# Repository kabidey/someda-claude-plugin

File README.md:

# someda for Claude Code

**Describe a circuit; get a fab-ready KiCad project with every claim checked.**

This plugin puts the [someda](https://github.com/kabidey/someda) engine behind three slash
commands. In a conversation, Claude writes the circuit as a small JSON plan: real parts with
datasheet pinouts, nets, and intent such as "USB-C on the top edge". Never a coordinate. The
compiled engine does the rest: schematic, footprints, placement, routing (differential pairs,
enforced crosstalk spacing), signal-integrity / stability / thermal audits, KiCad's own ERC and
DRC, Gerbers, drill, BOM, a JLCPCB order package and 3D renders. The build ends with six gates;
all six pass or the answer is **NOT DONE** with the failing gate named.

The engine repairs what a plan edit can fix (a misspelled footprint, a missing decoupling
capacitor, a regulator short of output capacitance, a connector with no room on its edge) and
builds again, so the plan can come from a small model, a large one, or a person.

## Install

```bash
claude plugin marketplace add kabidey/someda-claude-plugin
claude plugin install someda@someda
```

On first use the plugin resolves the engine: `someda` on your PATH, a `SOMEDA_BIN` override, or
the release binary for your platform (Linux x86_64, macOS Apple silicon and Intel, Windows
x86_64; other platforms are built from source with `cargo`). It also installs what a build
needs beyond the binary: KiCad's footprint and 3D model libraries (`apt` on Debian/Ubuntu) and
the LCSC/EasyEDA converter in a private virtualenv.

You need [KiCad](https://www.kicad.org/) with `kicad-cli` on your PATH (developed and verified
against KiCad 10.0.6). No API key is required: Claude is the planner.

Not using Claude Code? The same release archive the plugin downloads also holds `someda-app`,
a desktop window that does the whole flow with any language model provider (see the
[engine README](https://github.com/kabidey/someda#the-desktop-app)).

## What a session looks like

```
you:     /pcb-plan a 555 timer blinking an LED at about 1 Hz, 5 V in on a header
claude:  writes plan.json (NE555, timing RC, LED and resistor, 100 nF next to the 555,
         a 2-pin header on the left edge) and shows it for review

you:     /pcb-build 555 LED blinker
claude:  1. schematic written and exported to PDF for your approval
         2. fetch-libs: every footprint and 3D model FOUND or FETCHED (none MISSING)
         3. the engine builds: placement ✓  routed 15 of 15 ✓  audits ✓
            kicad-cli ERC ✓ DRC 0 errors ✓  Gerbers / drill / BOM / JLCPCB package / renders ✓
            export preflight: drc shorts unrouted pours gerbers drill = 6 / 6
         → someda-build/circuit.kicad_pcb, fab/, fab/jlcpcb/, render/, plan.built.json
```

Those numbers are the engine's quick-start plan
([examples/plan_555.json](https://github.com/kabidey/someda/blob/master/examples/plan_555.json))
built with someda 0.7.0 and kicad-cli 10.0.6.

## Commands

| Command | What it does |
|---|---|
| `/pcb-plan <description>` | Write `plan.json` following the [contract](skills/someda/references/CONTRACT.md) and show it. No build. |
| `/pcb-build <description>` | Schematic for approval → libraries fetched → build with the engine's repair rounds → honest report of every stage and gate. |
| `/pcb-check <file>` | The engine's DRC/ERC on an existing `.kicad_pcb` or `.kicad_sch`. |

The build step in detail:

1. **Schematic first.** The engine writes a readable schematic (library symbols, labelled pins) and stops; Claude exports it to PDF and asks you to approve or change the plan.
2. **Libraries.** `scripts/fetch-libs.py` pulls every footprint and 3D model the plan needs that your KiCad libraries lack: KiCad's GitLab repositories, LCSC/EasyEDA by `lcsc` part number (or `mpn`, resolved through JLCPCB's parts search), and KiCad zips you downloaded from UltraLibrarian, SnapEDA, Mouser or Digi-Key (`--import`). Every part ends **FOUND**, **FETCHED** (with its source) or **MISSING** with the plan edit to make. A MISSING name that is only a misspelling is corrected by the engine's first repair round; a part the libraries really lack is never guessed.
3. **Build.** `someda ai build` runs up to `SOMEDA_REPAIR_ROUNDS` (default 3) repair rounds by itself, printing `repair:` for what it changed and `suggest:` with the exact plan edit for what it could not; the plan as built is `someda-build/plan.built.json`.
4. **Report.** Claude reads the stage table and the audits and tells you what passed, what the warnings mean physically, and where the files are. It never claims done when a gate failed.

## What the engine does

Placement from real courtyards (mounting holes at their corners, edge connectors rotated so
their opening faces the edge and placed on it, parts next to the pins they share, keep-out
rings for fine-pitch escapes); routing on JLCPCB rules for 2, 4 or 6 layers with inner planes
and per-pad fanouts, escape vias for fine-pitch pins, differential pairs as coupled corridors
with matched lengths, 3W/5W crosstalk spacing enforced for every fast net; audits on the routed
copper (stray L/C, SWR, unterminated lines, crosstalk re-measured, decoupling loop inductance,
regulator and crystal checks, PDN |Z(f)|, junction temperatures, JLCPCB scope); kicad-cli ERC and
DRC judged from the report file; Gerbers, drill, position, detailed BOM, JLCPCB order package
(Protel-named zip, assembly BOM, CPL with rotation corrections), 3D renders with component
bodies. The [engine README](https://github.com/kabidey/someda#readme) has the full list and the
plan fields.

## A real board

[examples/sompi-v3s](examples/sompi-v3s) is an Allwinner V3s single-board computer planned this
way: 132 parts on 90 × 60 mm, six layers, USB-C, 10/100 Ethernet, microSD, SPI NOR, 40-pin LCD
and 24-pin MIPI camera FPCs, audio jack, GPIO header, two bucks and two LDOs. With someda 0.7.0
it routes 187 of 187 connections, couples all seven USB / Ethernet / MIPI pairs within their skew
budgets, has 0 crosstalk violations and kicad-cli DRC 0 errors, and passes the six gates. The
engine rotated every edge connector from its footprint, moved the audio jack to the bottom edge
when the top edge had no slot deep enough, and grew the 1.8 V plane island to reach its
capacitors. Its remaining warnings are real and listed (crystal traces of 11–17 mm, one far
capacitor, three capacitors beyond the island, board density 147 %).

The unedited outputs of that build (Gerbers, KiCad project, DRC and ERC reports, schematic PDF,
renders, BOM, JLCPCB package, checksums) are in
[examples/sompi-v3s/evidence](examples/sompi-v3s/evidence).

## What "six gates" does not mean

The boards are not simulated and have not been built. Connector pinouts follow conventions that
must be checked against the parts you buy; 3D bodies fetched from LCSC are not verified against
physical parts; clock-to-data skew across pairs is not enforced; everything is placed on the
top side. Read the warnings; they are the engine telling you what it could not make good.

## Repository

```
commands/            pcb-plan, pcb-build, pcb-check
skills/someda/       SKILL.md: how Claude plans and runs a build; references/CONTRACT.md: the plan
scripts/             setup-someda.sh (engine + libraries), fetch-libs.py (footprints and 3D models)
examples/sompi-v3s/  the SBC plan, its generator, design notes and build evidence
```

MIT license · [SomTronics](https://somtronics.org)

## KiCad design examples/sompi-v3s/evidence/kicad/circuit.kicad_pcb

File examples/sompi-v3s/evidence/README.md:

# Build evidence — SomPi-V3s

Unedited outputs of one `someda ai build` run of `../plan.json`, kept here so the result in the
README can be checked rather than believed. Nothing in this directory was hand-edited after the
build. This is the 0.7.0 build: every differential pair routed as a coupled pair with its
measured intra-pair skew, 3W/5W crosstalk spacing enforced by the router and re-measured by the
audit, and the oscillation checks (termination, decoupling loops, regulators, crystals, PDN)
in the stage table.

## Provenance

| What | Value |
|---|---|
| Date | 2026-10-19 |
| Engine | kabidey/someda commit `1d11b951fee7` (Cargo version 0.7.0), `cargo build --release` |
| Plan | `examples/sompi-v3s/plan.json` from `gen_sompi.py` |
| Verifier | kicad-cli 10.0.6 (ERC, DRC with zones refilled, Gerber/drill/position/BOM export with solder mask subtracted from silk, 3D render) |
| Gerber renders | gerbonara 1.6.3 reading the files in `fab/` |
| Pair cross-sections | JLCPCB impedance calculator (jlcpcb.com/pcb-impedance-calculator, 2026-10-19), JLC06161H-3313 L1/L2: 90 Ω w 0.1466 / s 0.1778 mm, 100 Ω w 0.1191 / s 0.2032 mm |
| Command | `SOMEDA_FOOTPRINT_DIRS=../lib SOMEDA_PLAN_FILE=plan.json SOMEDA_PROJECT_DIR=out someda ai build "SomPi-V3s 6-layer SBC"` |

Reproduce: build the engine at that commit, run the command above in `examples/sompi-v3s/`, and
compare `SHA256SUMS` against your `out/fab/` and `out/circuit.kicad_*`. The engine is
deterministic (same plan in, same copper out); kicad-cli output may differ byte-wise between
KiCad versions in comments, timestamps and UUIDs, so compare the DRC summary and the Gerber
geometry rather than hashes when the KiCad version differs.

## Stage table (from `reports/build.log`)

```
  ✓ [plan] 132 components, 114 nets
  ✓ [footprints] 132 real KiCad library footprints, 6 copper layers
  ✓ [pin-coverage] every plan pin has a pad (500 pins across 132 footprints)
  ✓ [placement] placed 132 footprint(s) on 90x60mm, 128 hint(s), 0 courtyard overlap(s)
  ✓ [route] routed 187 of 187 connections (0 unrouted), 225 plane fanouts, 104 escape vias (32 unused)
  ✓ [pairs] 7 pair(s) declared, 7 trunk(s) coupled, 7 within skew budget
  ✓ [si-audit] 0 error(s), 2 warning(s); stray L/C measured per net
  ✓ [thermal-audit] 0 error(s), 1 warning(s)
  ✓ [stability-audit] 0 error(s), 5 warning(s): regulator output capacitance, crystal loads and traces, switch/feedback nodes
  ✓ [pdn-audit] 4 rail(s) swept 100 kHz–200 MHz, 0 above the ΔV/ΔI target (model: MLCC ESR/ESL classes + measured mounting loops; above 200 MHz the package/die decoupling owns the rail)
  ✓ [fab-scope] JLC06161H-3313: trace 0.127/0.127mm, via 0.35/0.2mm inside JLCPCB 6-layer scope (±10% impedance)
  ✓ [generate] wrote out/circuit.kicad_sch and out/circuit.kicad_pcb
  ✓ [kicad-erc] [exit 0]
  ✓ [kicad-drc] 0 error(s), 34 warning(s), 0 unconnected, 0 fab-blocking [silk_edge_clearance×2 via_dangling×32] [report circuit-drc.rpt]
  ✓ [export-gerbers] [exit 0] (13 Gerber layers written: 6 copper + mask/paste/silk/outline)
  ✓ [export-drill] [exit 0]
  ✓ [export-pos] [exit 0]
  ✓ [export-bom] [exit 0] — fab/bom-detailed.csv + fab/bom.md: 54 line items, 128 components, 8 with a part number
  ✓ [jlcpcb-package] fab/jlcpcb/jlcpcb-gerbers.zip (15 files: Protel names, no X2, mask-subtracted silk, merged Excellon + map), jlcpcb-bom.csv (54 lines, 4 with an LCSC part), jlcpcb-cpl.csv (125 SMD parts, rotation corrections on 11: D1 +180°, D2 +180°, Q1 +180°, U1 +270°, U2 +180°, U3 +180°, U4 +180°, U5 +180°, U6 +270°, U8 +180°, Y1 +180°) — check the SMT preview before ordering
  ✓ [render] render/board-top.png render/board-bottom.png render/board-iso.png — component bodies from /usr/share/kicad/3dmodels (128 of 128 referenced models found)
  ✓ [someda-erc] 5 finding(s) [5 = known power-symbol gap (M4)]
  ✓ [someda-drc] 0 error(s), 0 warning(s)
  ✓ [export-preflight] drc=PASS shorts=PASS unrouted=PASS pours=PASS gerbers=PASS drill=PASS
```

## Differential pairs (measured on the routed copper)

```
pair USB_DP_J/USB_DM_J: coupled 10.5 mm on F.Cu, tails ≤ 1.5 mm, len P 12.71 / N 13.35 mm, skew -0.649 mm (budget 1.100), 3 corner(s), 0 bump(s)
pair USB_DP/USB_DM: coupled 9.7 mm on F.Cu, tails ≤ 7.6 mm, len P 19.20 / N 18.67 mm, skew +0.522 mm (budget 1.100), 5 corner(s), 0 bump(s), P/N order differs at the two ends: far tails cross through a via
pair ETH_TXP/ETH_TXN: coupled 16.1 mm on F.Cu, tails ≤ 4.1 mm, len P 20.92 / N 20.91 mm, skew +0.010 mm (budget 0.250), 3 corner(s), 0 bump(s)
pair ETH_RXP/ETH_RXN: coupled 14.6 mm on F.Cu, tails ≤ 10.5 mm, len P 32.61 / N 32.60 mm, skew +0.010 mm (budget 0.250), 3 corner(s), 0 bump(s)
pair CAM_MCSI_D0P/CAM_MCSI_D0N: coupled 46.1 mm on F.Cu, tails ≤ 1.7 mm, len P 48.92 / N 48.92 mm, skew +0.000 mm (budget 0.150), 4 corner(s), 1 bump(s)
pair CAM_MCSI_D1P/CAM_MCSI_D1N: coupled 45.3 mm on F.Cu, tails ≤ 1.1 mm, len P 47.53 / N 47.53 mm, skew -0.000 mm (budget 0.150), 8 corner(s), 0 bump(s)
pair CAM_MCSI_CKP/CAM_MCSI_CKN: coupled 38.7 mm on F.Cu, tails ≤ 8.4 mm, len P 48.16 / N 48.16 mm, skew +0.000 mm (budget 0.150), 4 corner(s), 0 bump(s)
```

## Audit findings (errors and warnings, from `reports/build.log`)

```
[warning] decoupling-loop C14 (GND/+1V8): 3.90nH mounting loop — stubs 0.1mm (0.04nH) + 5.1mm (1.73nH), via pair 2.12nH; via / via
[warning] decoupling-loop C58 (GND/+1V8): 7.37nH mounting loop — stubs 0.1mm (0.04nH) + 22.7mm (4.16nH), via pair 3.17nH; via / via
[warning] density-too-high (board): density 147% > 70% — thermal crowding and router pain
[warning] switch-node U2_SW: 23.9 mm of copper, 2 via(s) — the di/dt loop: keep short (≤ 15 mm) and away from FB
[warning] crystal-trace X24M_IN: 10.7 mm, 2 via(s) — crystal nets: ≤ 10 mm, no vias, nothing fast nearby (18 pF load)
[warning] crystal-trace X24M_OUT: 14.4 mm, 3 via(s) — crystal nets: ≤ 10 mm, no vias, nothing fast nearby (18 pF load)
[warning] crystal-trace X32K_IN: 16.5 mm, 4 via(s) — crystal nets: ≤ 10 mm, no vias, nothing fast nearby (6 pF load)
[warning] crystal-trace X32K_OUT: 12.6 mm, 3 via(s) — crystal nets: ≤ 10 mm, no vias, nothing fast nearby (6 pF load)
```

## PDN per rail

```
[info] pdn +1V2: peak |Z| 0.191 Ω at 200.0 MHz vs target 0.480 Ω (10 capacitor(s))
[info] pdn +1V8: peak |Z| 0.390 Ω at 200.0 MHz vs target 1.034 Ω (8 capacitor(s))
[info] pdn +3V3: peak |Z| 0.127 Ω at 200.0 MHz vs target 2.853 Ω (13 capacitor(s))
[info] pdn VBUS: peak |Z| 0.601 Ω at 200.0 MHz vs target 3.571 Ω (1 capacitor(s))
```

## Contents

- `fab/` — the Gerber set (6 copper + mask/paste/silk/outline), Excellon drill + map, position file, kicad-cli BOM, and the detailed BOM `bom-detailed.csv` / `bom.md` (quantity, references, value, MPN, LCSC, package, footprint)
- `fab/jlcpcb/` — the JLCPCB order package: `jlcpcb-gerbers.zip` (Protel names, no X2, mask-subtracted silk, merged Excellon drill + map), `jlcpcb-bom.csv` (Comment, Designator, Footprint, LCSC Part #), `jlcpcb-cpl.csv` (Designator, Mid X, Mid Y, Layer, Rotation with the package rotation corrections the build log lists)
- `render/board-iso.png` — isometric 3D render with component bodies (KiCad packages3D plus the LCSC/EasyEDA models fetch-libs pulled for the USB-C, RJ45, audio jack and inductors; those four are flagged alignment-unverified)
- `kicad/` — the schematic, board and project kicad-cli judged
- `schematic/` — the schematic as kicad-cli exports it: PDF, per-sheet SVG, and the netlist it carries (the same connectivity the board was routed from)
- `reports/` — the build log and the kicad-cli DRC report
- `render/` — kicad-cli PNG renders, top and bottom
- `gerber-render/` — per-layer SVGs rendered from `fab/` by gerbonara
- `SHA256SUMS` — checksums of everything above

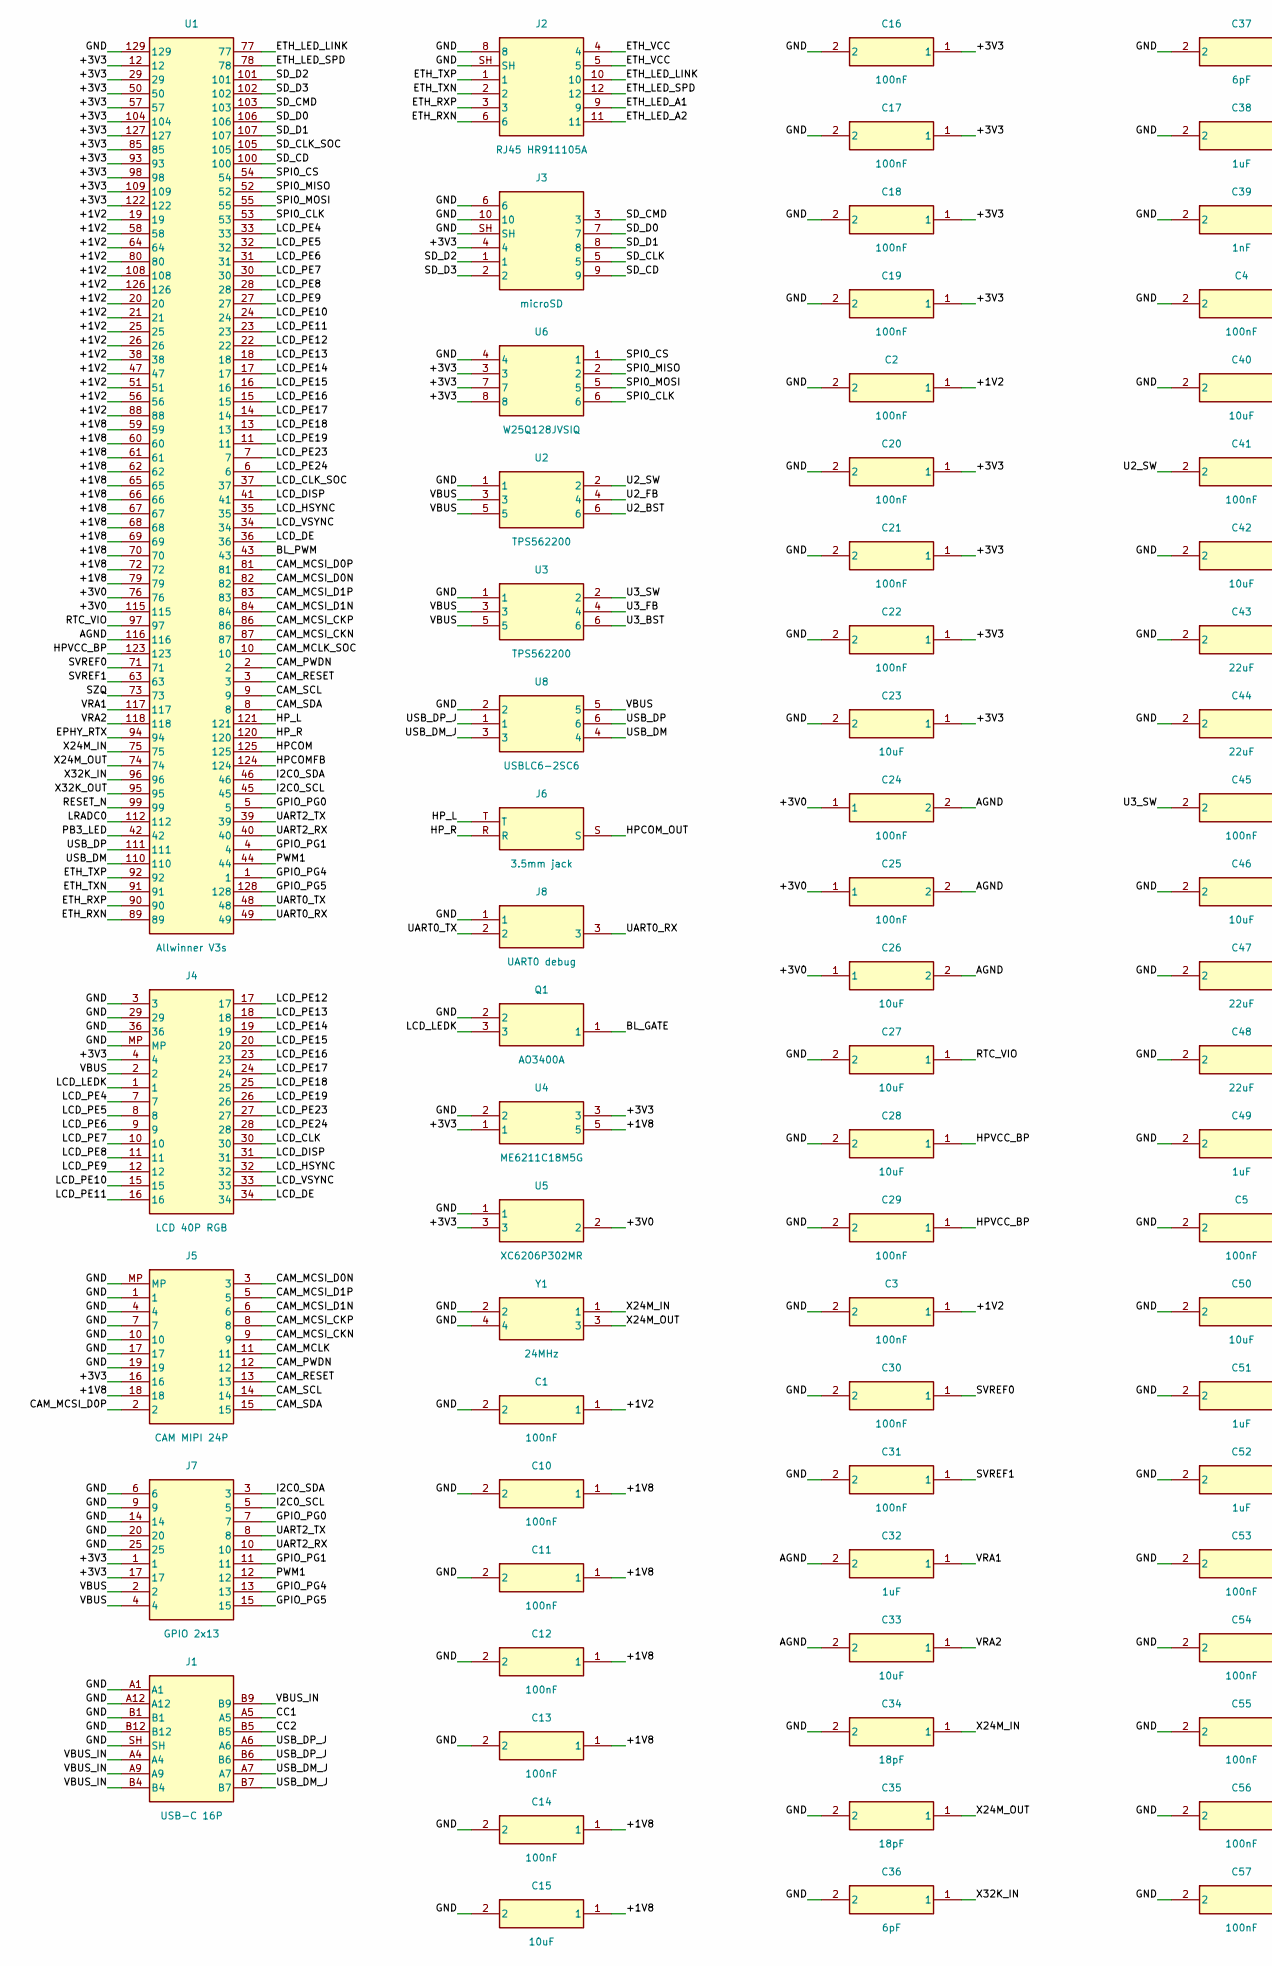
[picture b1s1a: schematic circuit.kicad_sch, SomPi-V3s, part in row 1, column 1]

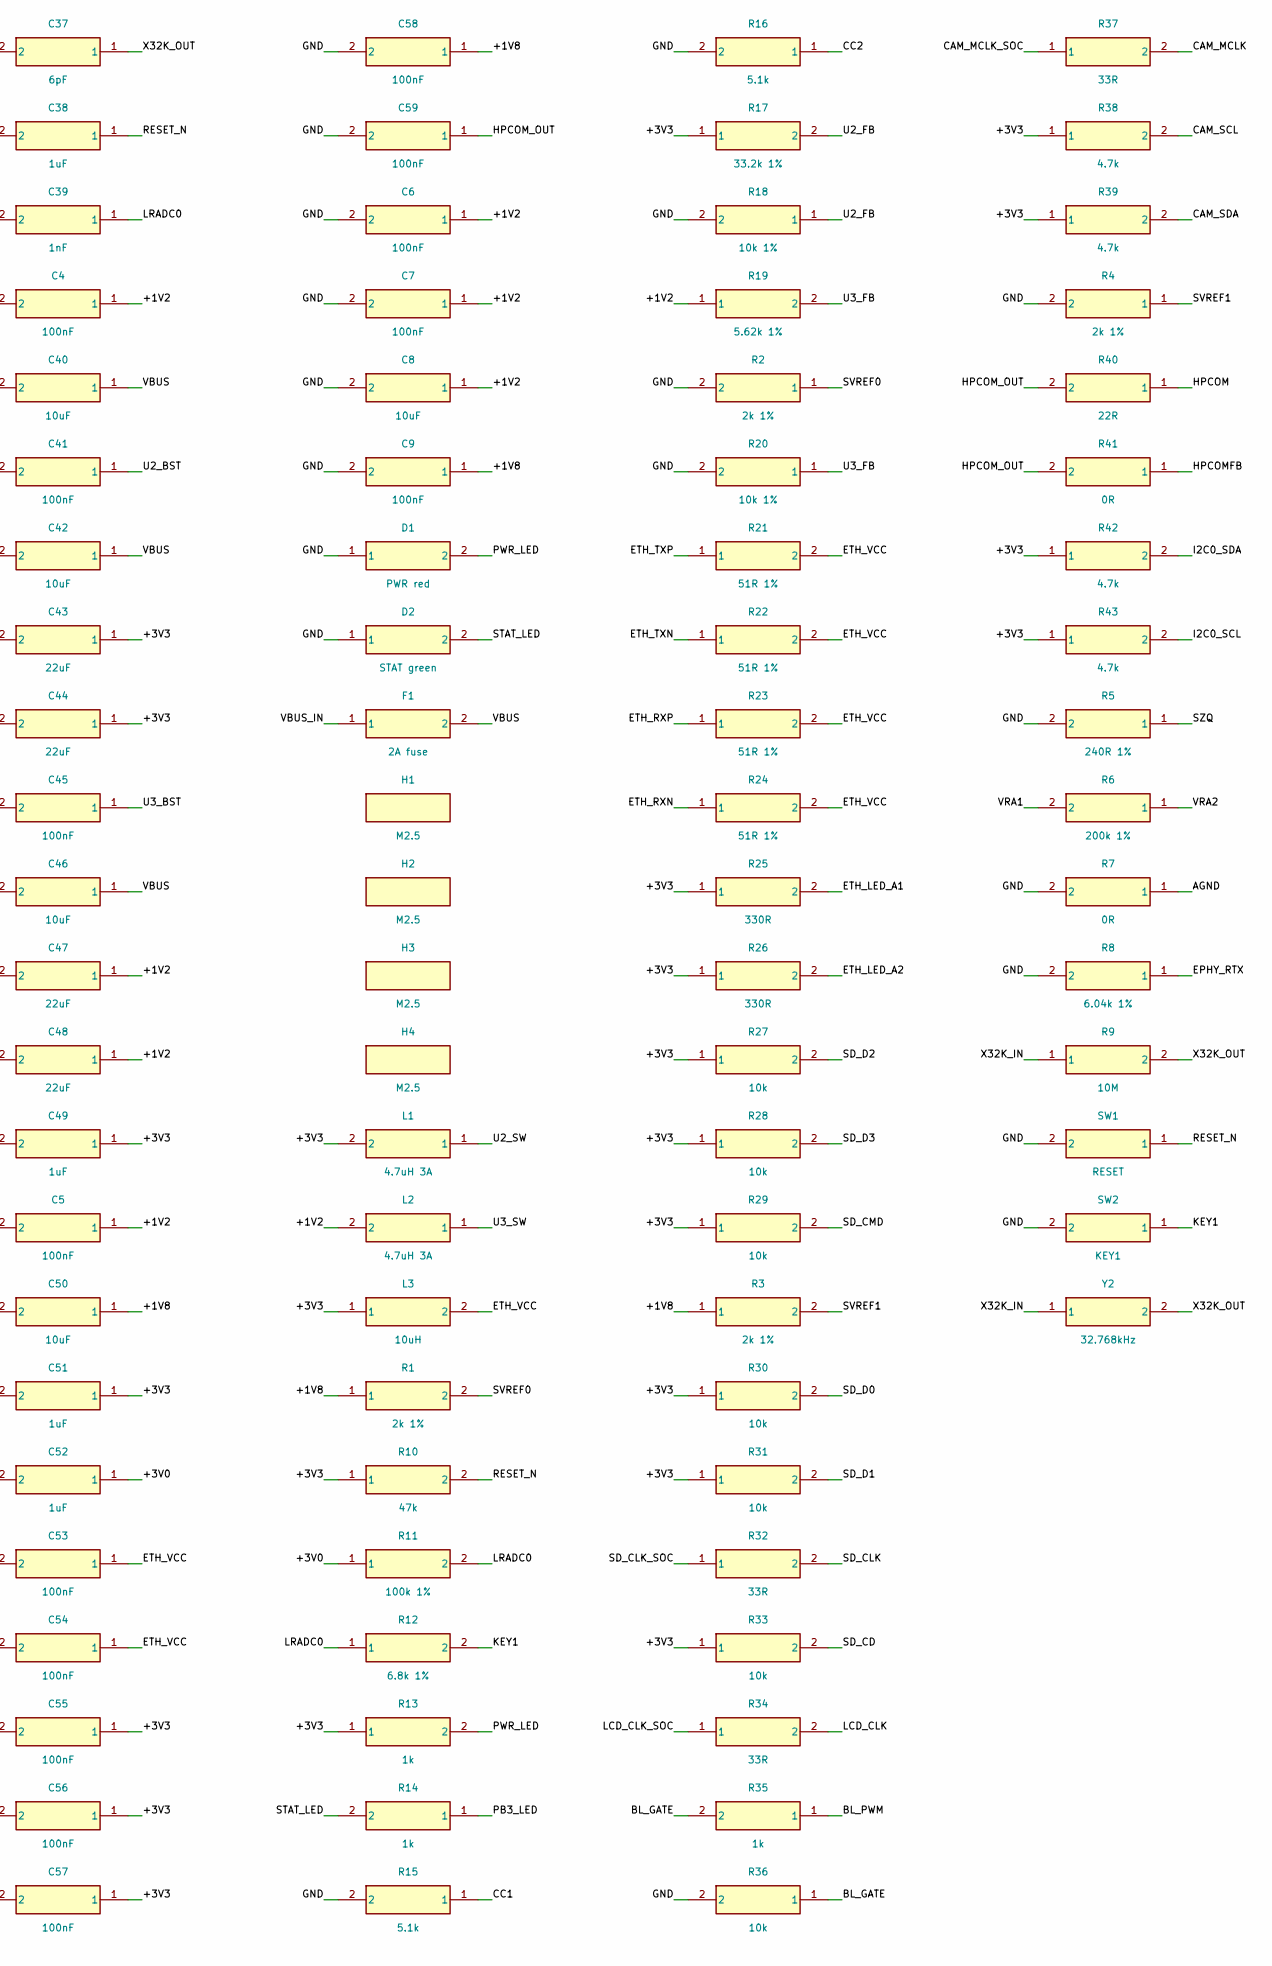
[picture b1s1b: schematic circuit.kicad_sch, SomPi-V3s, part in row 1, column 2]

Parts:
C1, C2, C3, C4, C5, C6, C7, C9, C10, C11, C12, C13, C14, C16, C17, C18, C19, C20, C21, C22, C24, C25, C29, C30, C31, C41, C45, C53, C54, C55, C56, C57, C58, C59: 100nF
C8, C15, C23, C26, C27, C28, C33, C40, C42, C46, C50: 10uF
C32, C38, C49, C51, C52: 1uF
C34, C35: 18pF
C36, C37: 6pF
C39: 1nF
C43, C44, C47, C48: 22uF
D1: PWR red
D2: STAT green
F1: 2A fuse
H1, H2, H3, H4: M2.5
J1: USB-C 16P
J2: RJ45 HR911105A
J3: microSD
J4: LCD 40P RGB
J5: CAM MIPI 24P
J6: 3.5mm jack
J7: GPIO 2x13
J8: UART0 debug
L1, L2: 4.7uH 3A
L3: 10uH
Q1: AO3400A
R1, R2, R3, R4: 2k 1%
R5: 240R 1%
R6: 200k 1%
R7, R41: 0R
R8: 6.04k 1%
R9: 10M
R10: 47k
R11: 100k 1%
R12: 6.8k 1%
R13, R14, R35: 1k
R15, R16: 5.1k
R17: 33.2k 1%
R18, R20: 10k 1%
R19: 5.62k 1%
R21, R22, R23, R24: 51R 1%
R25, R26: 330R
R27, R28, R29, R30, R31, R33, R36: 10k
R32, R34, R37: 33R
R38, R39, R42, R43: 4.7k
R40: 22R
SW1: RESET
SW2: KEY1
U1: Allwinner V3s
U2, U3: TPS562200
U4: ME6211C18M5G
U5: XC6206P302MR
U6: W25Q128JVSIQ
U8: USBLC6-2SC6
Y1: 24MHz
Y2: 32.768kHz

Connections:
+1V2: C1.1, C2.1, C3.1, C4.1, C5.1, C6.1, C7.1, C8.1, C47.1, C48.1, L2.2, R19.1, U1.19, U1.20, U1.21, U1.25, U1.26, U1.38, U1.47, U1.51, U1.56, U1.58, U1.64, U1.80, U1.88, U1.108, U1.126
+1V8: C9.1, C10.1, C11.1, C12.1, C13.1, C14.1, C15.1, C50.1, C58.1, J5.18, R1.1, R3.1, U1.59, U1.60, U1.61, U1.62, U1.65, U1.66, U1.67, U1.68, U1.69, U1.70, U1.72, U1.79, U4.5
+3V0: C24.1, C25.1, C26.1, C52.1, R11.1, U1.76, U1.115, U5.2
+3V3: C16.1, C17.1, C18.1, C19.1, C20.1, C21.1, C22.1, C23.1, C43.1, C44.1, C49.1, C51.1, C55.1, C56.1, C57.1, J3.4, J4.4, J5.16, J7.1, J7.17, L1.2, L3.1, R10.1, R13.1, R17.1, R25.1, R26.1, R27.1, R28.1, R29.1, R30.1, R31.1, R33.1, R38.1, R39.1, R42.1, R43.1, U1.12, U1.29, U1.50, U1.57, U1.85, U1.93, U1.98, U1.104, U1.109, U1.122, U1.127, U4.1, U4.3, U5.3, U6.3, U6.7, U6.8
AGND: C24.2, C25.2, C26.2, C32.2, C33.2, R7.1, U1.116
BL_GATE: Q1.1, R35.2, R36.1
BL_PWM: R35.1, U1.43
CAM_MCLK: J5.11, R37.2
CAM_MCLK_SOC: R37.1, U1.10
CAM_MCSI_CKN: J5.9, U1.87
CAM_MCSI_CKP: J5.8, U1.86
CAM_MCSI_D0N: J5.3, U1.82
CAM_MCSI_D0P: J5.2, U1.81
CAM_MCSI_D1N: J5.6, U1.84
CAM_MCSI_D1P: J5.5, U1.83
CAM_PWDN: J5.12, U1.2
CAM_RESET: J5.13, U1.3
CAM_SCL: J5.14, R38.2, U1.9
CAM_SDA: J5.15, R39.2, U1.8
CC1: J1.A5, R15.1
CC2: J1.B5, R16.1
EPHY_RTX: R8.1, U1.94
ETH_LED_A1: J2.9, R25.2
ETH_LED_A2: J2.11, R26.2
ETH_LED_LINK: J2.10, U1.77
ETH_LED_SPD: J2.12, U1.78
ETH_RXN: J2.6, R24.1, U1.89
ETH_RXP: J2.3, R23.1, U1.90
ETH_TXN: J2.2, R22.1, U1.91
ETH_TXP: J2.1, R21.1, U1.92
ETH_VCC: C53.1, C54.1, J2.4, J2.5, L3.2, R21.2, R22.2, R23.2, R24.2
GND: C1.2, C2.2, C3.2, C4.2, C5.2, C6.2, C7.2, C8.2, C9.2, C10.2, C11.2, C12.2, C13.2, C14.2, C15.2, C16.2, C17.2, C18.2, C19.2, C20.2, C21.2, C22.2, C23.2, C27.2, C28.2, C29.2, C30.2, C31.2, C34.2, C35.2, C36.2, C37.2, C38.2, C39.2, C40.2, C42.2, C43.2, C44.2, C46.2, C47.2, C48.2, C49.2, C50.2, C51.2, C52.2, C53.2, C54.2, C55.2, C56.2, C57.2, C58.2, C59.2, D1.1, D2.1, J1.A1, J1.A12, J1.B1, J1.B12, J1.SH, J2.8, J2.SH, J3.6, J3.10, J3.SH, J4.3, J4.29, J4.36, J4.MP, J5.1, J5.4, J5.7, J5.10, J5.17, J5.19, J5.MP, J7.6, J7.9, J7.14, J7.20, J7.25, J8.1, Q1.2, R2.2, R4.2, R5.2, R7.2, R8.2, R15.2, R16.2, R18.2, R20.2, R36.2, SW1.2, SW2.2, U1.129, U2.1, U3.1, U4.2, U5.1, U6.4, U8.2, Y1.2, Y1.4
GPIO_PG0: J7.7, U1.5
GPIO_PG1: J7.11, U1.4
GPIO_PG4: J7.13, U1.1
GPIO_PG5: J7.15, U1.128
HPCOM: R40.1, U1.125
HPCOMFB: R41.1, U1.124
HPCOM_OUT: C59.1, J6.S, R40.2, R41.2
HPVCC_BP: C28.1, C29.1, U1.123
HP_L: J6.T, U1.121
HP_R: J6.R, U1.120
I2C0_SCL: J7.5, R43.2, U1.45
I2C0_SDA: J7.3, R42.2, U1.46
KEY1: R12.2, SW2.1
LCD_CLK: J4.30, R34.2
LCD_CLK_SOC: R34.1, U1.37
LCD_DE: J4.34, U1.36
LCD_DISP: J4.31, U1.41
LCD_HSYNC: J4.32, U1.35
LCD_LEDK: J4.1, Q1.3
LCD_PE4: J4.7, U1.33
LCD_PE5: J4.8, U1.32
LCD_PE6: J4.9, U1.31
LCD_PE7: J4.10, U1.30
LCD_PE8: J4.11, U1.28
LCD_PE9: J4.12, U1.27
LCD_PE10: J4.15, U1.24
LCD_PE11: J4.16, U1.23
LCD_PE12: J4.17, U1.22
LCD_PE13: J4.18, U1.18
LCD_PE14: J4.19, U1.17
LCD_PE15: J4.20, U1.16
LCD_PE16: J4.23, U1.15
LCD_PE17: J4.24, U1.14
LCD_PE18: J4.25, U1.13
LCD_PE19: J4.26, U1.11
LCD_PE23: J4.27, U1.7
LCD_PE24: J4.28, U1.6
LCD_VSYNC: J4.33, U1.34
LRADC0: C39.1, R11.2, R12.1, U1.112
PB3_LED: R14.1, U1.42
PWM1: J7.12, U1.44
PWR_LED: D1.2, R13.2
RESET_N: C38.1, R10.2, SW1.1, U1.99
RTC_VIO: C27.1, U1.97
SD_CD: J3.9, R33.2, U1.100
SD_CLK: J3.5, R32.2
SD_CLK_SOC: R32.1, U1.105
SD_CMD: J3.3, R29.2, U1.103
SD_D0: J3.7, R30.2, U1.106
SD_D1: J3.8, R31.2, U1.107
SD_D2: J3.1, R27.2, U1.101
SD_D3: J3.2, R28.2, U1.102
SPI0_CLK: U1.53, U6.6
SPI0_CS: U1.54, U6.1
SPI0_MISO: U1.52, U6.2
SPI0_MOSI: U1.55, U6.5
STAT_LED: D2.2, R14.2
SVREF0: C30.1, R1.2, R2.1, U1.71
SVREF1: C31.1, R3.2, R4.1, U1.63
SZQ: R5.1, U1.73
U2_BST: C41.1, U2.6
U2_FB: R17.2, R18.1, U2.4
U2_SW: C41.2, L1.1, U2.2
U3_BST: C45.1, U3.6
U3_FB: R19.2, R20.1, U3.4
U3_SW: C45.2, L2.1, U3.2
UART0_RX: J8.3, U1.49
UART0_TX: J8.2, U1.48
UART2_RX: J7.10, U1.40
UART2_TX: J7.8, U1.39
USB_DM: U1.110, U8.4
USB_DM_J: J1.A7, J1.B7, U8.3
USB_DP: U1.111, U8.6
USB_DP_J: J1.A6, J1.B6, U8.1
VBUS: C40.1, C42.1, C46.1, F1.2, J4.2, J7.2, J7.4, U2.3, U2.5, U3.3, U3.5, U8.5
VBUS_IN: F1.1, J1.A4, J1.A9, J1.B4, J1.B9
VRA1: C32.1, R6.2, U1.117
VRA2: C33.1, R6.1, U1.118
X24M_IN: C34.1, U1.75, Y1.1
X24M_OUT: C35.1, U1.74, Y1.3
X32K_IN: C36.1, R9.1, U1.96, Y2.1
X32K_OUT: C37.1, R9.2, U1.95, Y2.2

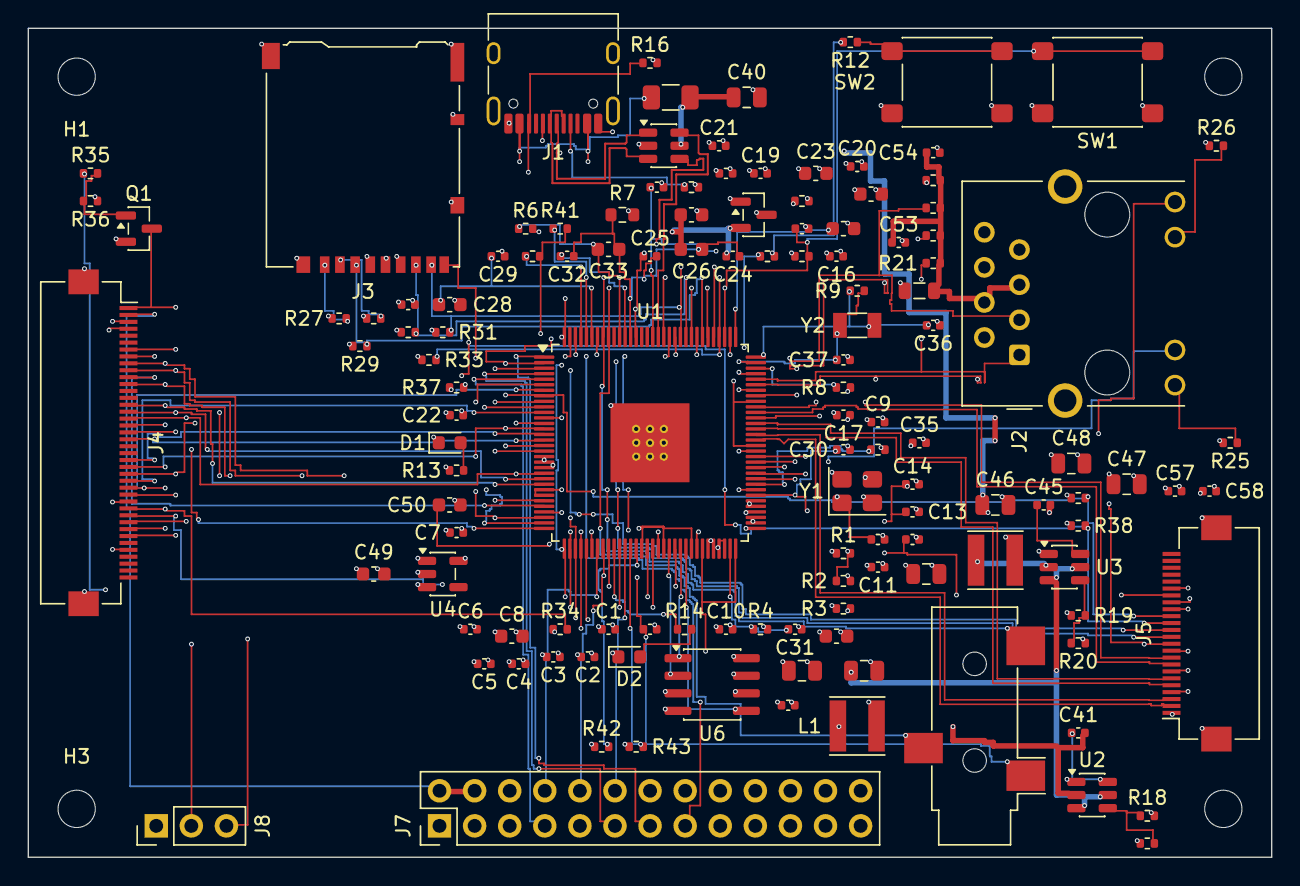
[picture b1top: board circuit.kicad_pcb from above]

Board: 6 copper layers, 90.0 x 60.0 mm, 132 parts (0 on the bottom side), 114 nets.
